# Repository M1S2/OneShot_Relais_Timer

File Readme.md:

# OneShot Relais Timer

This is a relais timer module that switches a AC mains load ON for a defined period of time.

## PCB
The schematics and PCBs were created using EAGLE. They were designed to be manufactured using toner transfer method so all traces are as big as possible.

There are two PCBs:
- The Main_PCB contains the microcontroller, the relay and the transformer and regulators used to generate all needed voltages.

- The UI_PCB contains the buttons, the 7-segment display and the needed BCD-7-segment driver IC.

## Housing
The housing of a mechanical timer was used to containg the PCBs.
The following parts are needed additionally:
- 1x Grundplatte.stl
- 1x Abdeckung_Symbole.stl (should be printed with 2 colors)
- 3x Spacer.stl
- 3x Screw M3x30
- 1x Screw M3x12
- 4x Sheet Metal Screw 15mm long

## Software
The software was written for the ATTiny204 microcontroller.

A statemachine is running in the main loop with the following two states:
- SET: The hours can be modified using the set button. The allowed range is 0 to 9. If the start/stop button is pressed, the relay is toggled and the state is changed to COUNTDOWN.
- COUNTDOWN: If the remaining seconds are equal 0 (counted by the PIT interrupt) or the start/stop button is pressed, the relay is toggled and the state is changed to SET.

It uses the following peripherals:
- TCA0: Timer used to query the buttons. It calls the button debounce routine of Peter Dannegger (http://www.mikrocontroller.net/articles/Entprellung).
- PIT: Periodic Interrupt Timer used to count the remaining seconds in COUNTDOWN mode. It also toggles the 7-segment dot in COUNTDOWN mode.

### 0-hours
If the hours are set to 0, the start/stop button can be used to directly toggle the relay. By toggling the relay, an inverted mode is activated, because the relay is toggled when the (normal) countdown is started.
E.g.:
- The set button is used to set the hours to 0
- The start/stop button is used to toggle the relay on.
- The set button is used to set the hours to e.g. 1
- The start/stop button is used to start the countdown > the relay is switched off and on after 1 hour (inverted mode)

### Last set hour
The last set hours are saved when the Countdown is started and are reload on startup.

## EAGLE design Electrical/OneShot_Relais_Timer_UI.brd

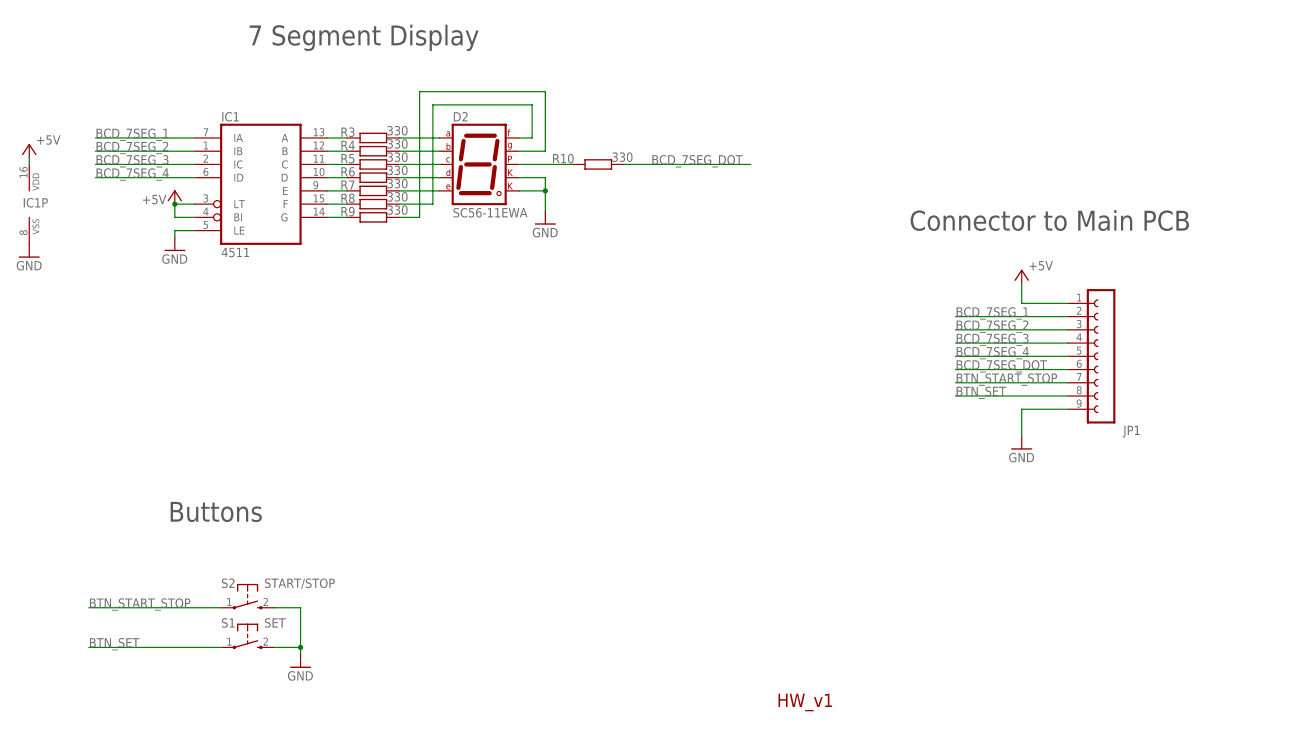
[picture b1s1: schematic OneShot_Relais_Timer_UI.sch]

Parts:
D2: SC56-11EWA; 7SEG-13
IC1: 4511; SOIC127P1032X265-16L
JP1: FE09-1; FE09
R3, R4, R5, R6, R7, R8, R9, R10: 330; R0805
S1: SET; B3F-10XX
S2: START/STOP; B3F-10XX

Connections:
+5V: IC1.3 (LT), IC1.4 (BI), IC1.16 (VDD), JP1.1
BCD_7SEG_1: IC1.7 (IA), JP1.2
BCD_7SEG_2: IC1.1 (IB), JP1.3
BCD_7SEG_3: IC1.2 (IC), JP1.4
BCD_7SEG_4: IC1.6 (ID), JP1.5
BCD_7SEG_DOT: JP1.6, R10.2
BTN_SET: JP1.8, S1.1
BTN_START_STOP: JP1.7, S2.1
GND: D2.3 (CK1), D2.8 (CK2), IC1.5 (LE), IC1.8 (VSS), JP1.9, S1.2 (S), S2.2 (S)
unnamed: D2.6 (B), R4.2
unnamed: IC1.13 (A), R3.1
unnamed: IC1.12 (B), R4.1
unnamed: IC1.11 (C), R5.1
unnamed: IC1.10 (D), R6.1
unnamed: IC1.9 (E), R7.1
unnamed: IC1.15 (F), R8.1
unnamed: IC1.14 (G), R9.1
unnamed: D2.7 (A), R3.2
unnamed: D2.4 (C), R5.2
unnamed: D2.2 (D), R6.2
unnamed: D2.1 (E), R7.2
unnamed: D2.9 (F), R8.2
unnamed: D2.10 (G), R9.2
unnamed: D2.5 (DP), R10.1

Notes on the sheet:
Buttons
7 Segment Display
Connector to Main PCB
HW_v1

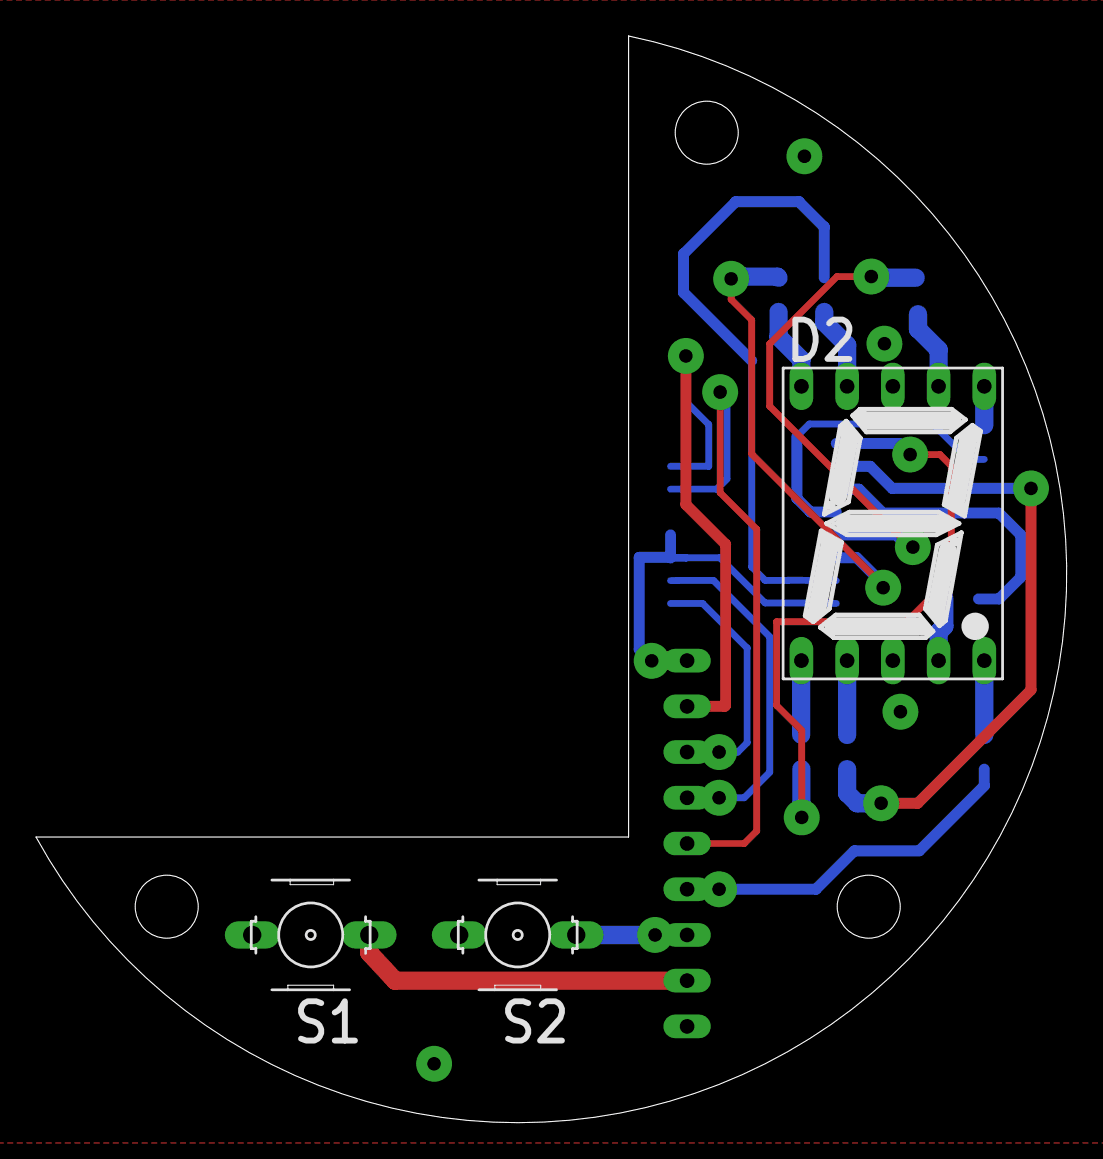
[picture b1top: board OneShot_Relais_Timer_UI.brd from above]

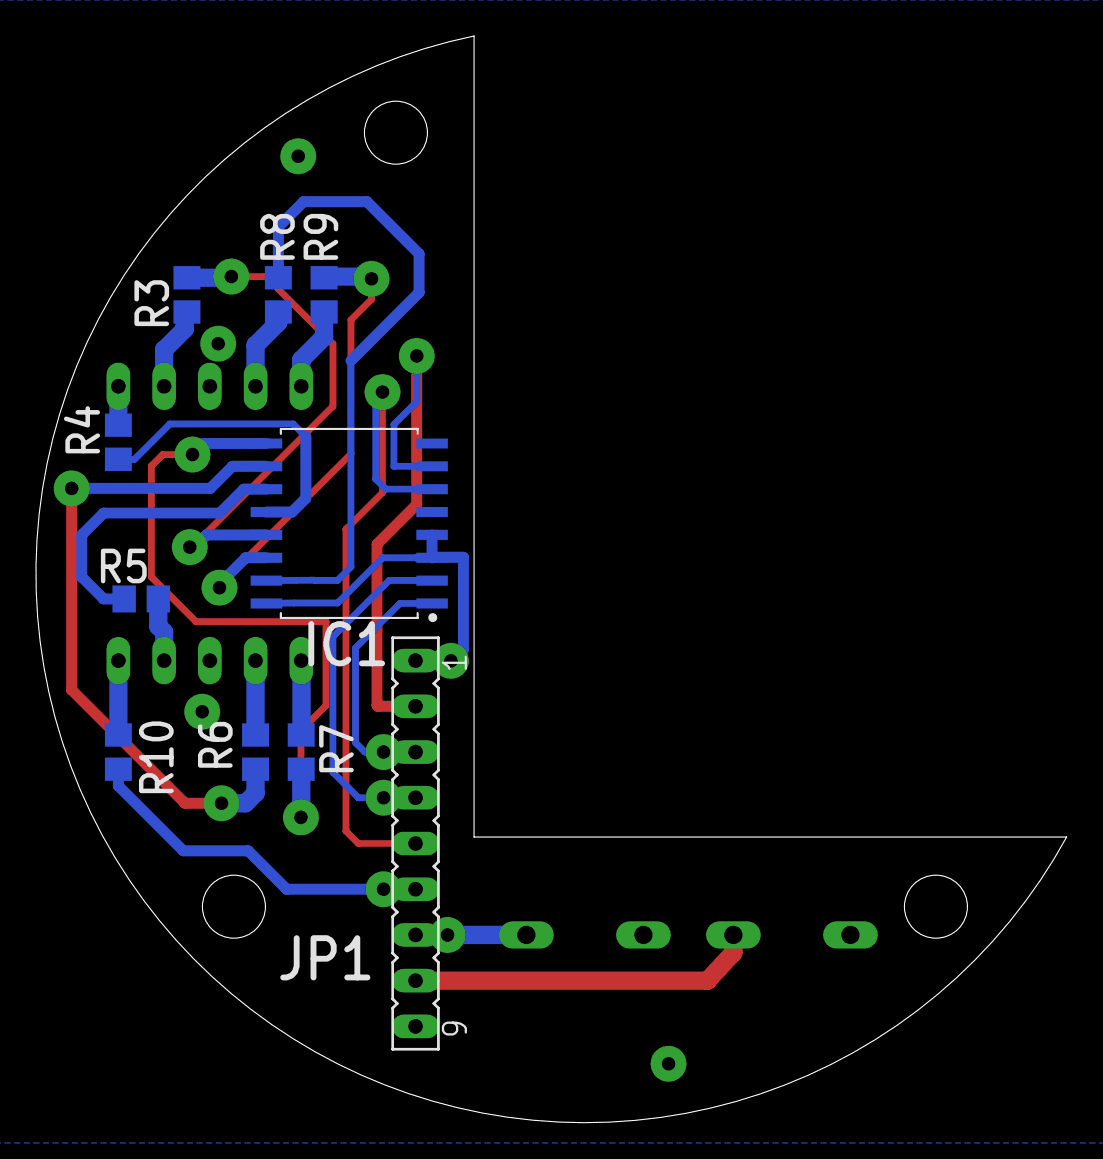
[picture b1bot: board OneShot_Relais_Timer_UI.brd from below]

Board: 2 copper layers, 57.3 x 60.4 mm, 13 parts (10 on the bottom side), 24 nets.

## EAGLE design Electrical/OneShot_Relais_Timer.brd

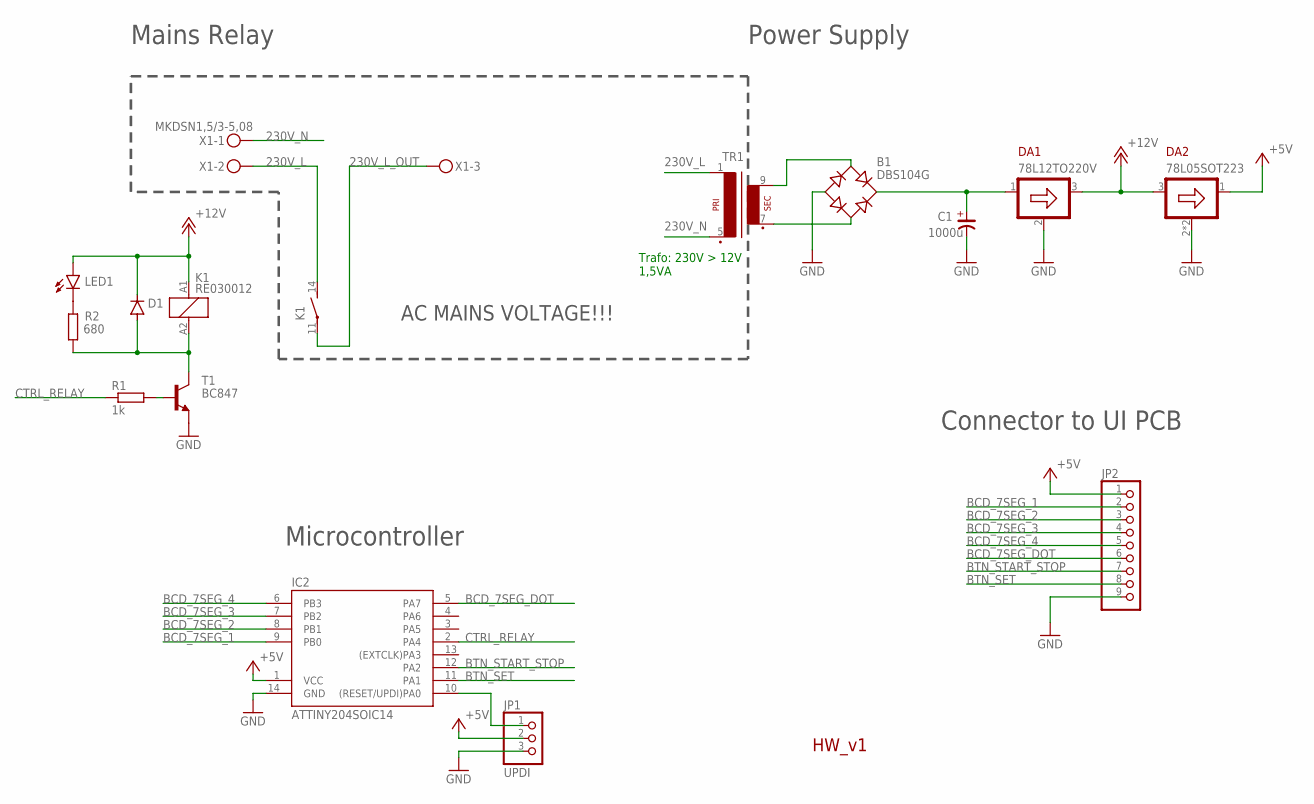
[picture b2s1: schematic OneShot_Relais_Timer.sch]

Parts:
B1: DBS104G; DBS
C1: 1000u; CSV-G
D1: DIODE-SOD80C; SOD80C
DA1: 78L12TO220V; TO220V
DA2: 78L05SOT223; SOT223
IC2: ATTINY204SOIC14; SOIC127P600X175-14N
JP1: UPDI; 1X03
JP2: PINHD-1X9; 1X09
K1: RE030012; RE-SCHRACK
LED1: LED5MM
R1: 1k; R0805
R2: 680; R0805
T1: BC847; SOT23
TR1: EI30-12.5; EI30-1
X1: MKDSN1,5/3-5,08

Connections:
230V_L: K1.14 (S), TR1.1, X1.2
230V_L_OUT: K1.11, X1.3
230V_N: TR1.5 (P2), X1.1
+5V: DA2.1 (OUT), IC2.1 (VCC), JP1.2, JP2.1
+12V: D1.C, DA1.3 (OUT), DA2.3 (IN), K1.A1 (1), LED1.A
BCD_7SEG_1: IC2.9 (PB0), JP2.2
BCD_7SEG_2: IC2.8 (PB1), JP2.3
BCD_7SEG_3: IC2.7 (PB2), JP2.4
BCD_7SEG_4: IC2.6 (PB3), JP2.5
BCD_7SEG_DOT: IC2.5 (PA7), JP2.6
BTN_SET: IC2.11 (PA1), JP2.8
BTN_START_STOP: IC2.12 (PA2), JP2.7
CTRL_RELAY: IC2.2 (PA4), R1.1
GND: B1.-, C1.-, DA1.2 (GND), DA2.2 (GND), DA2.4 (GND), IC2.14 (GND), JP1.3, JP2.9, T1.2 (E)
unnamed: R1.2, T1.1 (B)
unnamed: LED1.K (C), R2.2
unnamed: D1.A, K1.A2 (2), R2.1, T1.3 (C)
unnamed: B1.+, C1.+, DA1.1 (IN)
unnamed: B1.AC2, TR1.7 (S3)
unnamed: B1.AC1, TR1.9 (S4)
unnamed: IC2.10 ((RESET/UPDI)PA0), JP1.1

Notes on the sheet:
Trafo: 230V > 12V 1,5VA
AC MAINS VOLTAGE!!!
Microcontroller
Connector to UI PCB
Power Supply
Mains Relay
HW_v1

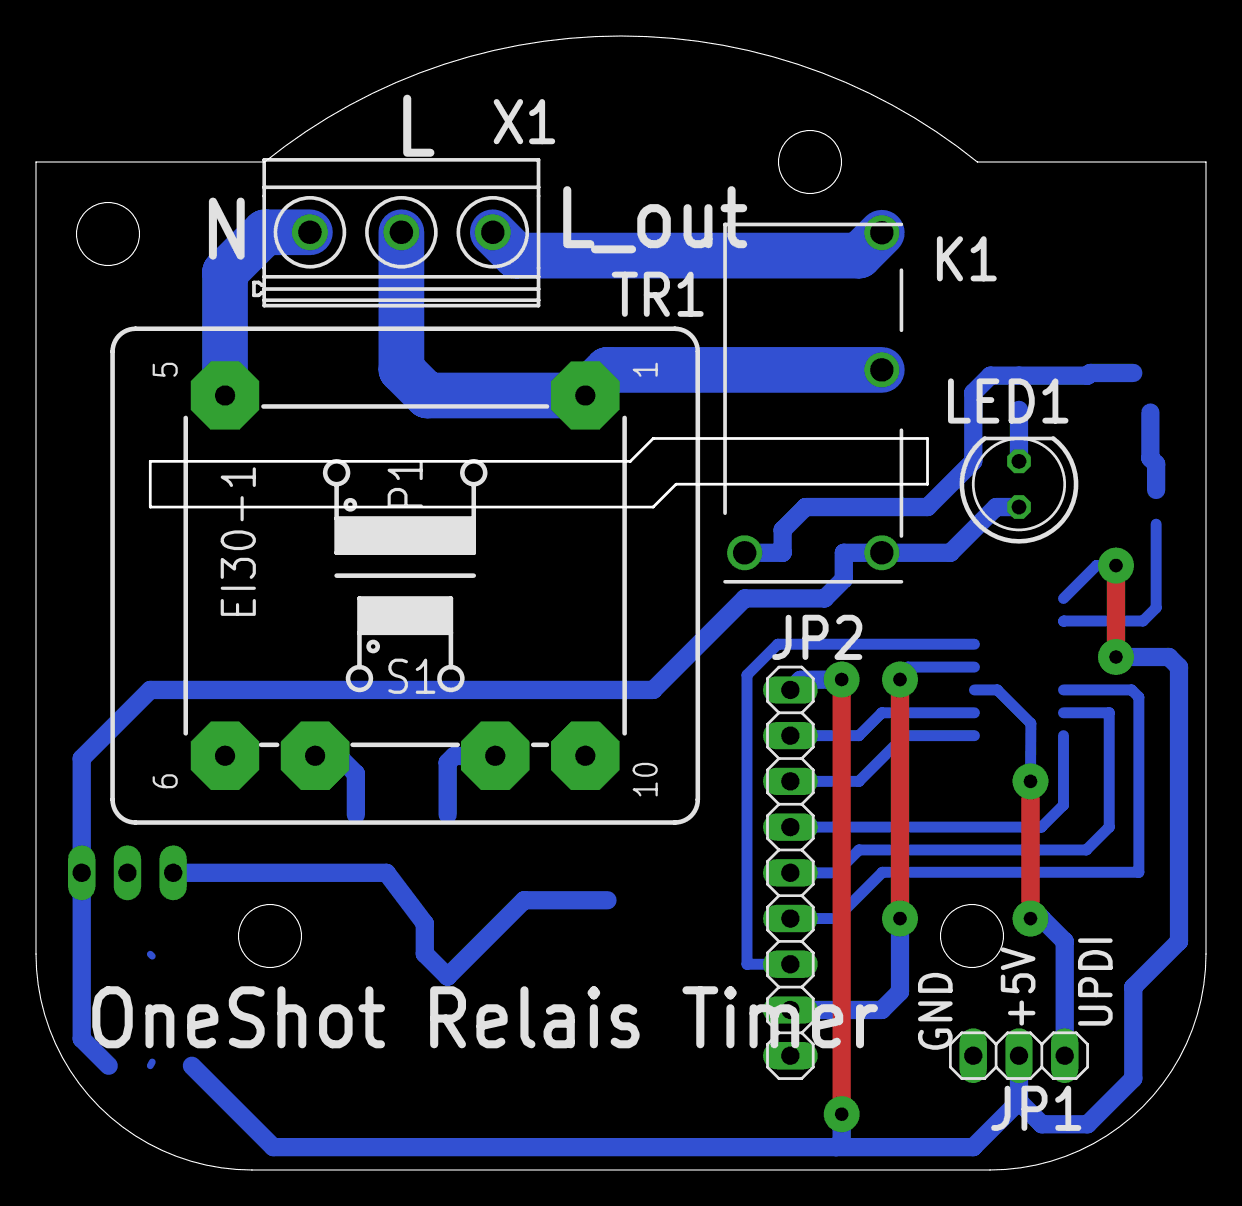
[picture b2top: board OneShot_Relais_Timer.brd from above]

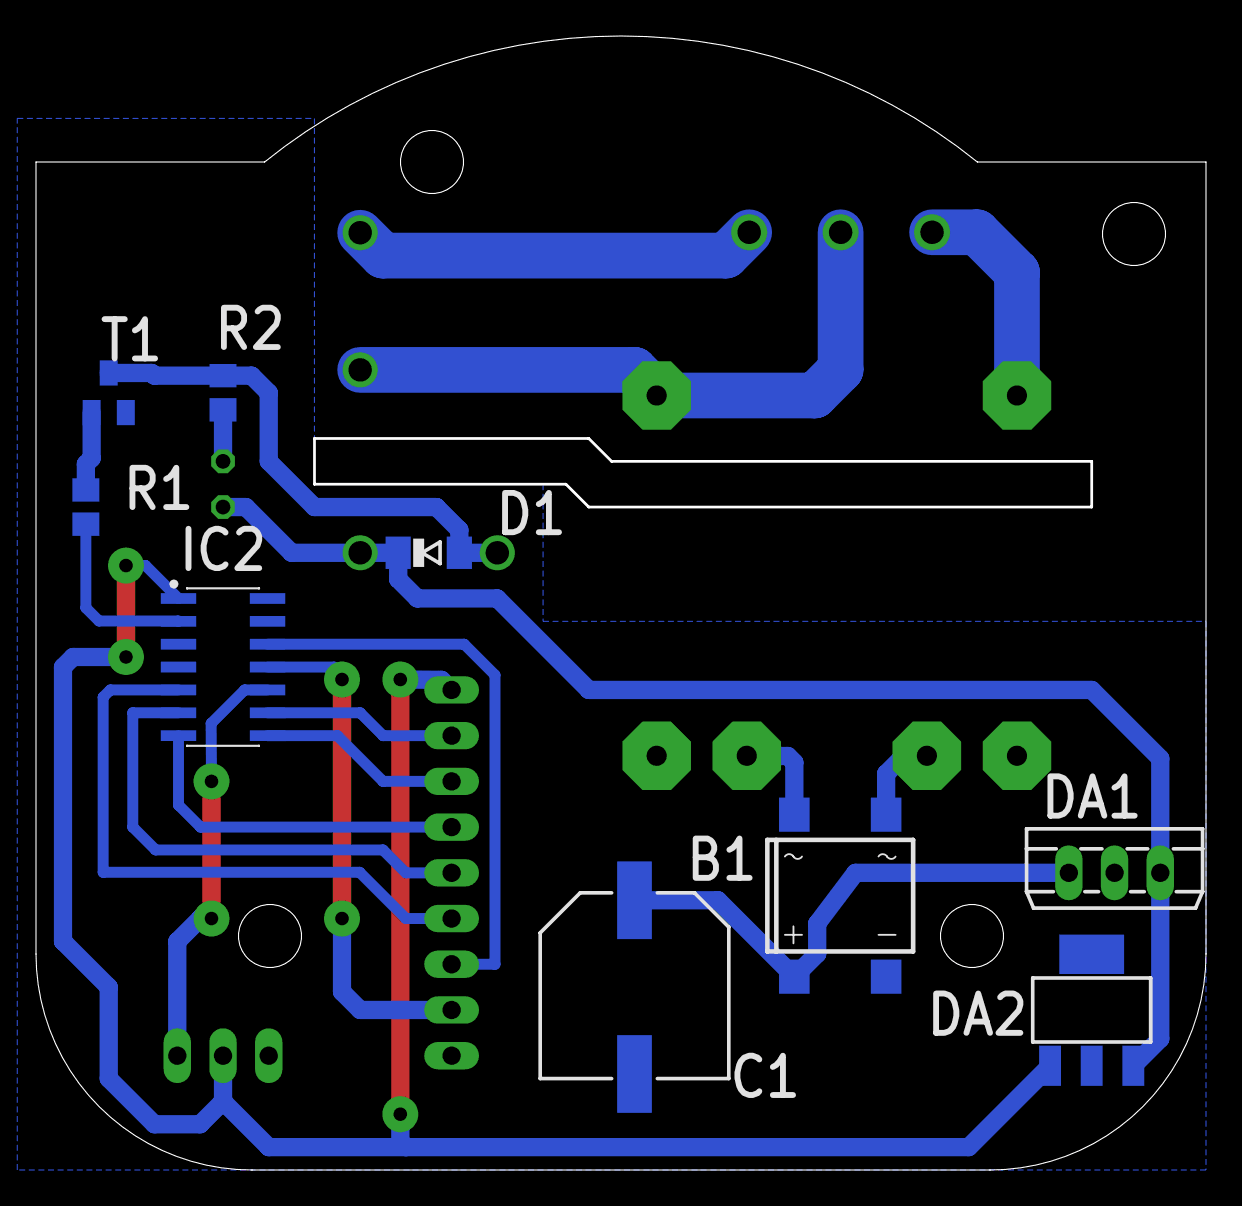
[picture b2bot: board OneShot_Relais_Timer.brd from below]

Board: 2 copper layers, 64.8 x 62.8 mm, 15 parts (9 on the bottom side), 21 nets.

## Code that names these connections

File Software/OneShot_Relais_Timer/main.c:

/*
 * OneShot_Relais_Timer.c
 *
 * Created: 09.10.2022 17:48:37
 * Author : Markus
 */ 

#define F_CPU 3333333UL		// 20 MHz / 6
#include <avr/io.h>
#include <util/delay.h>
#include <avr/interrupt.h>
#include <avr/eeprom.h>
#include "Buttons_Debounce.h"

// ################################################################################

#define PIN_CTRL_RELAY		PIN4_bp
#define PIN_BCD_7SEG_DOT	PIN7_bp

#define CTRL_RELAY_ON		PORTA_OUT |= (1<<PIN_CTRL_RELAY);
#define CTRL_RELAY_OFF		PORTA_OUT &= ~(1<<PIN_CTRL_RELAY);
#define CTRL_RELAY_TOGGLE	PORTA_OUT ^= (1<<PIN_CTRL_RELAY);

#define SET_7SEG(number)	PORTB_OUT = number;	
#define DOT_7SEG_ON			PORTA_OUT |= (1<<PIN_BCD_7SEG_DOT);
#define DOT_7SEG_OFF		PORTA_OUT &= ~(1<<PIN_BCD_7SEG_DOT);
#define DOT_7SEG_TOGGLE		PORTA_OUT ^= (1<<PIN_BCD_7SEG_DOT);
		
#define SECONDS_FOR_7SEG_DIGIT	3600		// This number of seconds must elapse for the 7 segment digit to change

// ################################################################################

typedef enum States
{
	STATE_SET,
	STATE_COUNTDOWN
}States_t;

volatile States_t currentState;

uint8_t setHours;
volatile uint16_t remainingSeconds;


EEMEM uint8_t ee_defaultHours;			// default number of hours that are read from / saved to EEPROM

// ################################################################################

/*************************************************
* ISR for the TCA0 Overflow
* This timer is used for button handling
**************************************************/
ISR(TCA0_OVF_vect)
{		
	debounce_timer_interrupt();	
	TCA0.SINGLE.INTFLAGS = TCA_SINGLE_OVF_bm;		//The interrupt flag has to be cleared manually (by writing a '1' to it)
}

/*************************************************
* ISR for the RTC PIT Interrupt
* This interrupt is used for counting seconds
**************************************************/
ISR(RTC_PIT_vect)
{
	if(currentState == STATE_COUNTDOWN)
	{
		DOT_7SEG_TOGGLE
		remainingSeconds--;
	}
	
	RTC.PITINTFLAGS = RTC_PI_bm;					//The interrupt flag has to be cleared manually (by writing a '1' to it)
}

// ################################################################################

int main(void)
{
	// Init IO registers
	PORTA_DIR &= ~PIN1_bm;				// Set BTN_SET Pin (PA1) as input
	PORTA_DIR &= ~PIN2_bm;				// Set BTN_START_STOP Pin (PA2) as input
	PORTA_DIR |= PIN4_bm;				// Set CTRL_RELAY Pin (PA4) as output
	PORTA_DIR |= PIN7_bm;				// Set BCD_7SEG_DOT Pin (PA7) as output
	PORTB_DIR = 0xF;					// Set BCD_7SEG_1 to BCD_7SEG_4 Pins (PB0..PB4) as outputs
	PORTA_PIN1CTRL |= PORT_PULLUPEN_bm;	// Enable Pull-Up for BTN_SET Pin (PA1)
	PORTA_PIN2CTRL |= PORT_PULLUPEN_bm;	// Enable Pull-Up for BTN_START_STOP Pin (PA2)

	// Init Timer (TCA0, used for button handling)
	TCA0.SINGLE.CTRLA = TCA_SINGLE_CLKSEL2_bm | TCA_SINGLE_CLKSEL1_bm | TCA_SINGLE_CLKSEL0_bm | TCA_SINGLE_ENABLE_bm;	// Set Prescaler to 1024 (CLKSEL=7 (Bits 3..1)), Enable Timer (Bit 0)
	TCA0.SINGLE.PER = (uint16_t)(F_CPU / 1024 * 10e-3 + 0.5);					// preload for 10 ms
	TCA0.SINGLE.INTCTRL = TCA_SINGLE_OVF_bm;									// Enable overflow interrupt
	
	// Init PIT (Periodic interrupt timer, used for counting seconds)
	RTC.CLKSEL = RTC_CLKSEL_INT1K_gc;						// Use internal 1.024 kHz clock
	RTC.PITINTCTRL = RTC_PI_bm;								// Enable PIT interrupt
	RTC.PITCTRLA = RTC_PERIOD_CYC1024_gc | RTC_PITEN_bm;	// Set period to 1024 clock cycles (every second) and enable the PIT

	sei();
	
	currentState = STATE_SET;
	setHours = eeprom_read_byte(&ee_defaultHours);	// read the default hours from the EEPROM
	if(setHours < 1 || setHours > 9)				// read value is out of valid range
	{
		setHours = 3;
	}
	remainingSeconds = 0;
	SET_7SEG(setHours)
	
	DOT_7SEG_OFF
	CTRL_RELAY_OFF
	
	while (1)
	{		
		switch(currentState)
		{
			case STATE_SET:
			{
				if(get_key_press(1 << KEY_SET) || get_key_rpt(1 << KEY_SET))
				{
					setHours++;
					setHours = setHours % 10;
					SET_7SEG(setHours)
				}
				else if(get_key_press(1 << KEY_START_STOP))
				{
					// If hours are set to 0, the relay can be toggled using the start stop button. The countdown can be changed from active during countdown to non-active during countdown.
					if(setHours == 0)
					{
						CTRL_RELAY_TOGGLE
					}
					else
					{
						eeprom_update_byte(&ee_defaultHours, setHours);		// write the setHours to the EEPROM as new default value
						currentState = STATE_COUNTDOWN;
						CTRL_RELAY_TOGGLE
					}
					
					remainingSeconds = setHours * SECONDS_FOR_7SEG_DIGIT;
				}
				else
				{
					// Nothing to do here
				}
				break;
			}
			case STATE_COUNTDOWN:
			{
				if(get_key_press(1 << KEY_START_STOP) || remainingSeconds <= 0)
				{
					currentState = STATE_SET;
					CTRL_RELAY_TOGGLE
					setHours = eeprom_read_byte(&ee_defaultHours);		// read the default hours from the EEPROM
					SET_7SEG(setHours)
					DOT_7SEG_OFF
				}
				else
				{
					SET_7SEG(remainingSeconds / SECONDS_FOR_7SEG_DIGIT)
				}
				
				get_key_press(1 << KEY_SET);		// This is only consumed here to not trigger the set button in SET mode after leaving COUNTDOWN mode (when button was pressed in COUNTDOWN mode)
				
				break;
			}
		}		
	}
}

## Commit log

2022-10-02 Initial version with first schematic draft
2022-10-04 First rough placement of components
2022-10-05 Replaced connectors for AC mains, replaced 12V regulator, added 3D models (trafo, relay, connector X1)
2022-10-06 Replaced 12V and 5V regulators, changed trafo type
2022-10-06 Moved UI components (7 segment, buttons) to separate PCB
2022-10-07 Added mounting holes to PCB, moved relay, small adaptions to UI PCB
2022-10-10 Added mounting hole to PCB
2022-10-13 Added GND planes, refined routing
2022-10-14 Added 3D model for C1 on PCB, improved routing of PCB
2022-10-16 Moved 12V regulator to other side, improved texts, improved UI PCB (increased vias and traces)
2022-10-18 Replaced BCD 7Segment IC with correct type (footprint), corrected routing of UI PCB
2022-10-19 Added mechanical models for housing
2022-10-22 Small adpation to Grundplatte
2022-12-11 Small adaptions to PCBs, schematics, and mechanical components
2022-12-11 Adapted first version for ATTiny204
2022-12-11 Added images and improved Readme
2022-12-11 Added calibration factor for time counting
2022-12-11 Modified Readme, added more comments to code
2022-12-11 Added 0-hours as feature to toggle the relay directly (and activate inverse mode)
2022-12-11 Using second timer to count seconds in COUNTDOWN state
2022-12-11 Corrected F_CPU
2022-12-11 Replaced timer TCB by Periodic Interrupt Timer (PIT)
2022-12-11 Removed some not used defines, corrected one small bug (ignore SET button in COUNTDOWN state)
2022-12-11 Persist default hours to EEPROM
2022-12-11 Added button debounce code
2022-12-11 First version of software (developed on ATMega16)
